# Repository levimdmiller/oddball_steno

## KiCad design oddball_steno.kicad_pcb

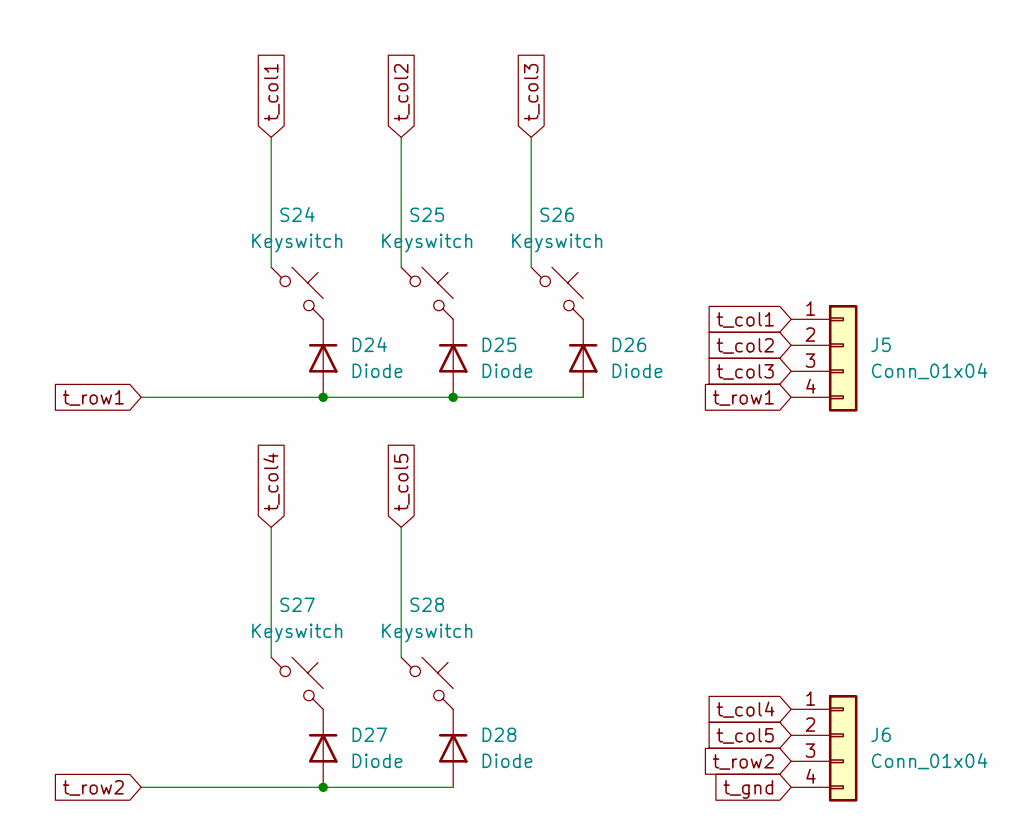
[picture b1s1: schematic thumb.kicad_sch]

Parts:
D24, D25, D26, D27, D28: Diode; Diode_DO-35
J5, J6: Conn_01x04; SolderWire-0.5sqmm_1x04_P4.6mm_D0.9mm_OD2.1mm
S24, S25, S26, S27, S28: Keyswitch; MX_PCB_1.00u

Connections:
unnamed: D24.1 (K), S24.2
unnamed: D25.1 (K), S25.2
unnamed: D26.1 (K), S26.2
unnamed: D27.1 (K), S27.2
unnamed: D28.1 (K), S28.2
t_col1: J5.1, S24.1
t_col2: J5.2, S25.1
t_col3: J5.3, S26.1
t_col4: J6.1, S27.1
t_col5: J6.2, S28.1
t_gnd: J6.4
t_row1: D24.2 (A), D25.2 (A), D26.2 (A), J5.4
t_row2: D27.2 (A), D28.2 (A), J6.3

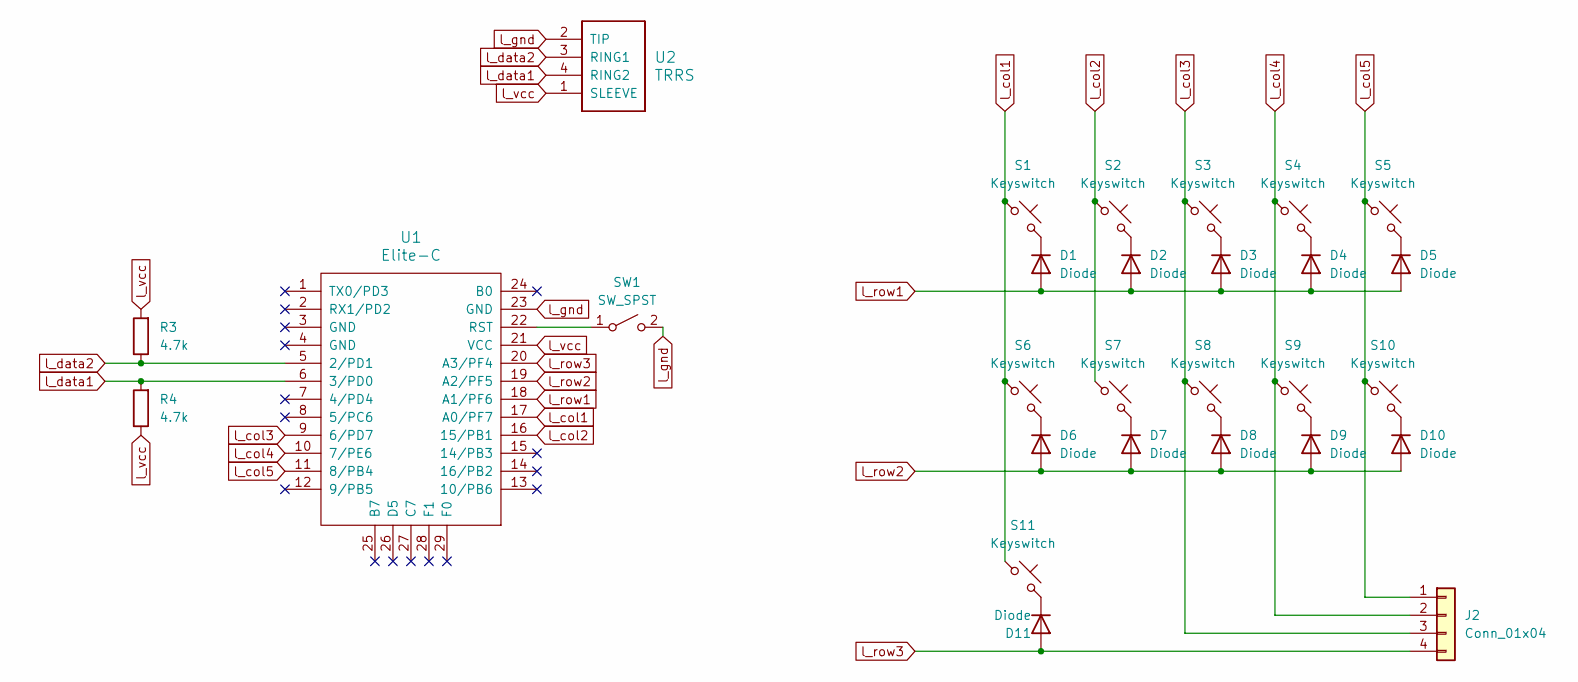
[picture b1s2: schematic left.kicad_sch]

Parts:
D1, D2, D3, D4, D5, D6, D7, D8, D9, D10, D11: Diode; Diode_DO-35
J2: Conn_01x04; SolderWire-0.5sqmm_1x04_P4.6mm_D0.9mm_OD2.1mm
R3, R4: 4.7k; Resistor
S1: Keyswitch; MX_PCB_4.00u
S2, S3, S4, S5, S7, S8, S9, S10: Keyswitch; MX_PCB_1.00u
S6, S11: Keyswitch; MX_PCB_2.00u_90deg
SW1: SW_SPST; SW_Push_1P1T_NO_CK_KSC6xxJ
U1: Elite-C
U2: TRRS; TRRS_PJ-320A

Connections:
unnamed: D1.1 (K), S1.2
unnamed: D2.1 (K), S2.2
unnamed: D3.1 (K), S3.2
unnamed: D4.1 (K), S4.2
unnamed: D5.1 (K), S5.2
unnamed: D6.1 (K), S6.2
unnamed: D7.1 (K), S7.2
unnamed: D8.1 (K), S8.2
unnamed: D9.1 (K), S9.2
unnamed: D10.1 (K), S10.2
unnamed: D11.1 (K), S11.2
unnamed: SW1.1 (A), U1.22 (RST)
l_col1: S1.1, S6.1, S11.1, U1.17 (A0/PF7)
l_col2: S2.1, S7.1, U1.16 (15/PB1)
l_col3: J2.3, S3.1, S8.1, U1.9 (6/PD7)
l_col4: J2.2, S4.1, S9.1, U1.10 (7/PE6)
l_col5: J2.1, S5.1, S10.1, U1.11 (8/PB4)
l_data1: R4.2, U1.6 (3/PD0), U2.4 (RING2)
l_data2: R3.1, U1.5 (2/PD1), U2.3 (RING1)
l_gnd: SW1.2 (B), U1.23 (GND), U2.2 (TIP)
l_row1: D1.2 (A), D2.2 (A), D3.2 (A), D4.2 (A), D5.2 (A), U1.18 (A1/PF6)
l_row2: D6.2 (A), D7.2 (A), D8.2 (A), D9.2 (A), D10.2 (A), U1.19 (A2/PF5)
l_row3: D11.2 (A), J2.4, U1.20 (A3/PF4)
l_vcc: R3.2, R4.1, U1.21 (VCC), U2.1 (SLEEVE)

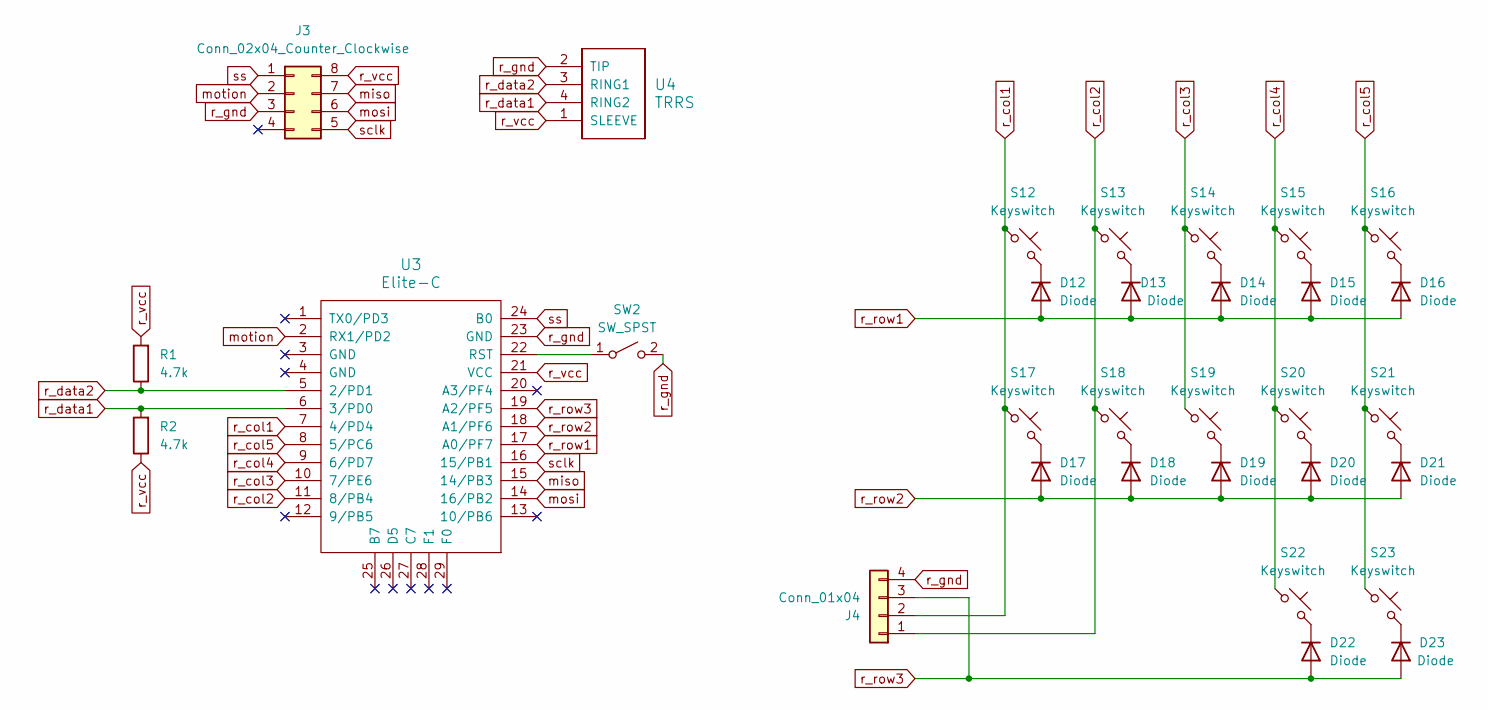
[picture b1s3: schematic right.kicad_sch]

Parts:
D12, D13, D14, D15, D16, D17, D18, D19, D20, D21, D22, D23: Diode; Diode_DO-35
J3: Conn_02x04_Counter_Clockwise; PinHeader_2x04_P2.54mm_Vertical
J4: Conn_01x04; SolderWire-0.5sqmm_1x04_P4.6mm_D0.9mm_OD2.1mm
R1, R2: 4.7k; Resistor
S12, S13, S14, S15, S16, S17, S18, S19, S20, S21: Keyswitch; MX_PCB_1.00u
S22: Keyswitch; MX_PCB_2.00u_90deg
S23: Keyswitch; MX_PCB_6.00u
SW2: SW_SPST; SW_Push_1P1T_NO_CK_KSC6xxJ
U3: Elite-C
U4: TRRS; TRRS_PJ-320A

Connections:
unnamed: D12.1 (K), S12.2
unnamed: D13.1 (K), S13.2
unnamed: D14.1 (K), S14.2
unnamed: D15.1 (K), S15.2
unnamed: D16.1 (K), S16.2
unnamed: D17.1 (K), S17.2
unnamed: D18.1 (K), S18.2
unnamed: D19.1 (K), S19.2
unnamed: D20.1 (K), S20.2
unnamed: D21.1 (K), S21.2
unnamed: D22.1 (K), S22.2
unnamed: D23.1 (K), S23.2
unnamed: SW2.1 (A), U3.22 (RST)
miso: J3.7, U3.15 (14/PB3)
mosi: J3.6, U3.14 (16/PB2)
motion: J3.2, U3.2 (RX1/PD2)
r_col1: J4.2, S12.1, S17.1, U3.7 (4/PD4)
r_col2: J4.1, S13.1, S18.1, U3.11 (8/PB4)
r_col3: S14.1, S19.1, U3.10 (7/PE6)
r_col4: S15.1, S20.1, S22.1, U3.9 (6/PD7)
r_col5: S16.1, S21.1, S23.1, U3.8 (5/PC6)
r_data1: R2.2, U3.6 (3/PD0), U4.4 (RING2)
r_data2: R1.1, U3.5 (2/PD1), U4.3 (RING1)
r_gnd: J3.3, J4.4, SW2.2 (B), U3.23 (GND), U4.2 (TIP)
r_row1: D12.2 (A), D13.2 (A), D14.2 (A), D15.2 (A), D16.2 (A), U3.17 (A0/PF7)
r_row2: D17.2 (A), D18.2 (A), D19.2 (A), D20.2 (A), D21.2 (A), U3.18 (A1/PF6)
r_row3: D22.2 (A), D23.2 (A), J4.3, U3.19 (A2/PF5)
r_vcc: J3.8, R1.2, R2.1, U3.21 (VCC), U4.1 (SLEEVE)
sclk: J3.5, U3.16 (15/PB1)
ss: J3.1, U3.24 (B0)

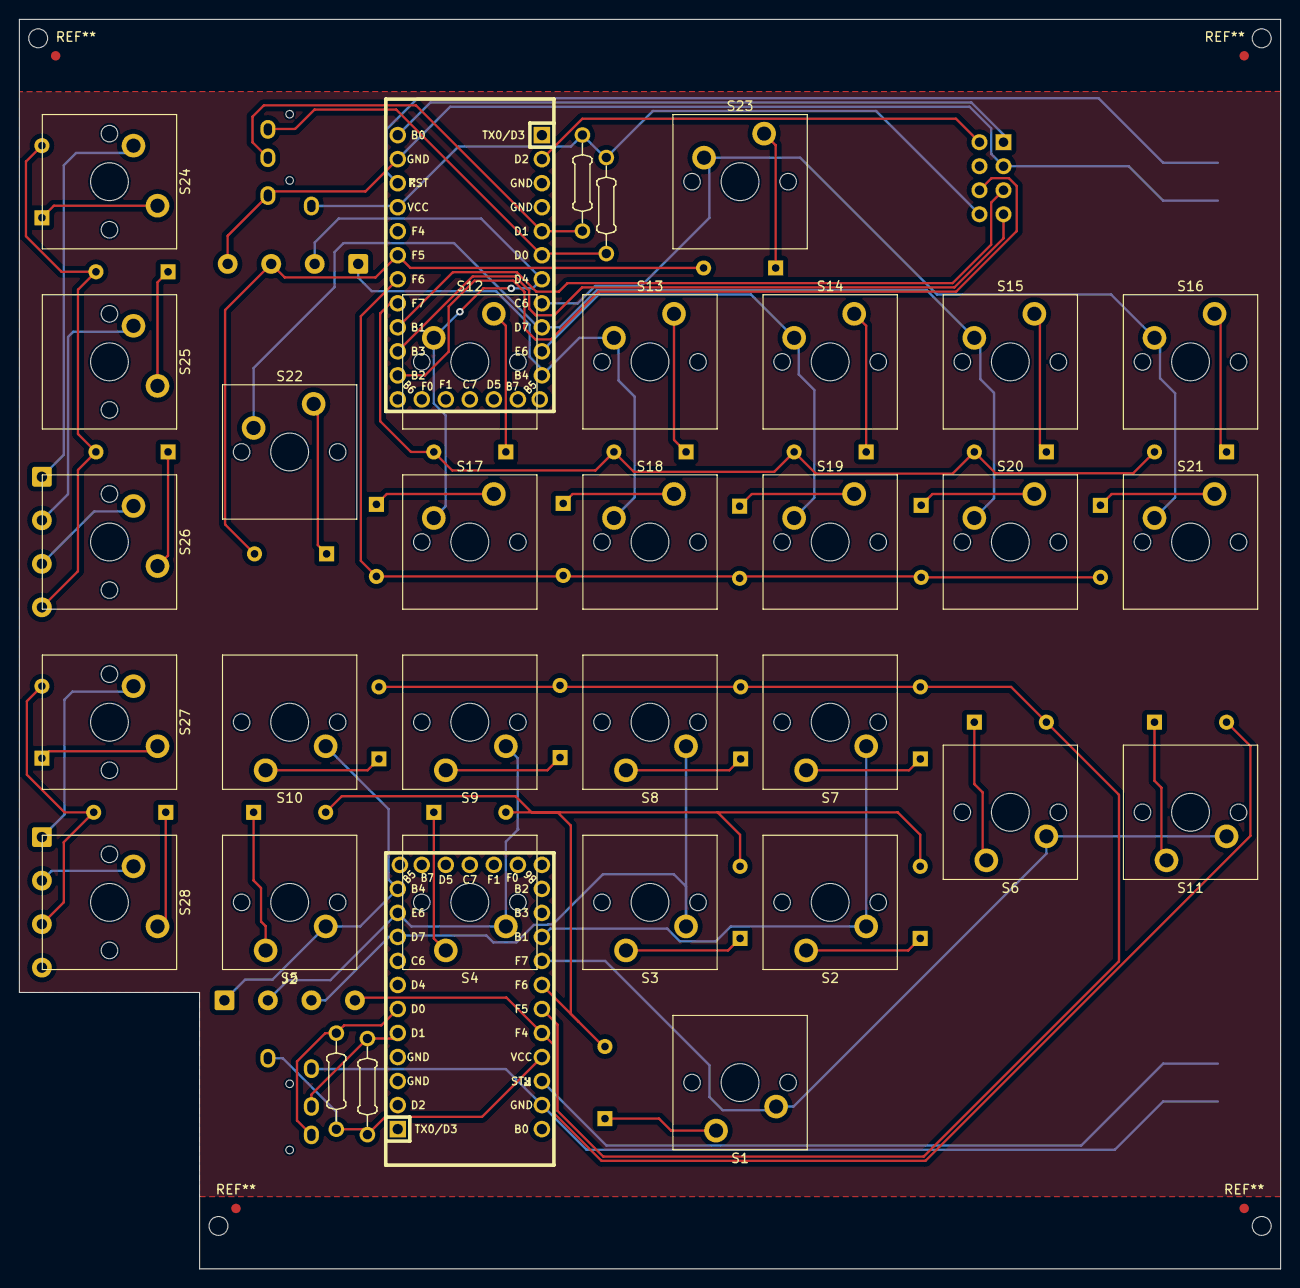
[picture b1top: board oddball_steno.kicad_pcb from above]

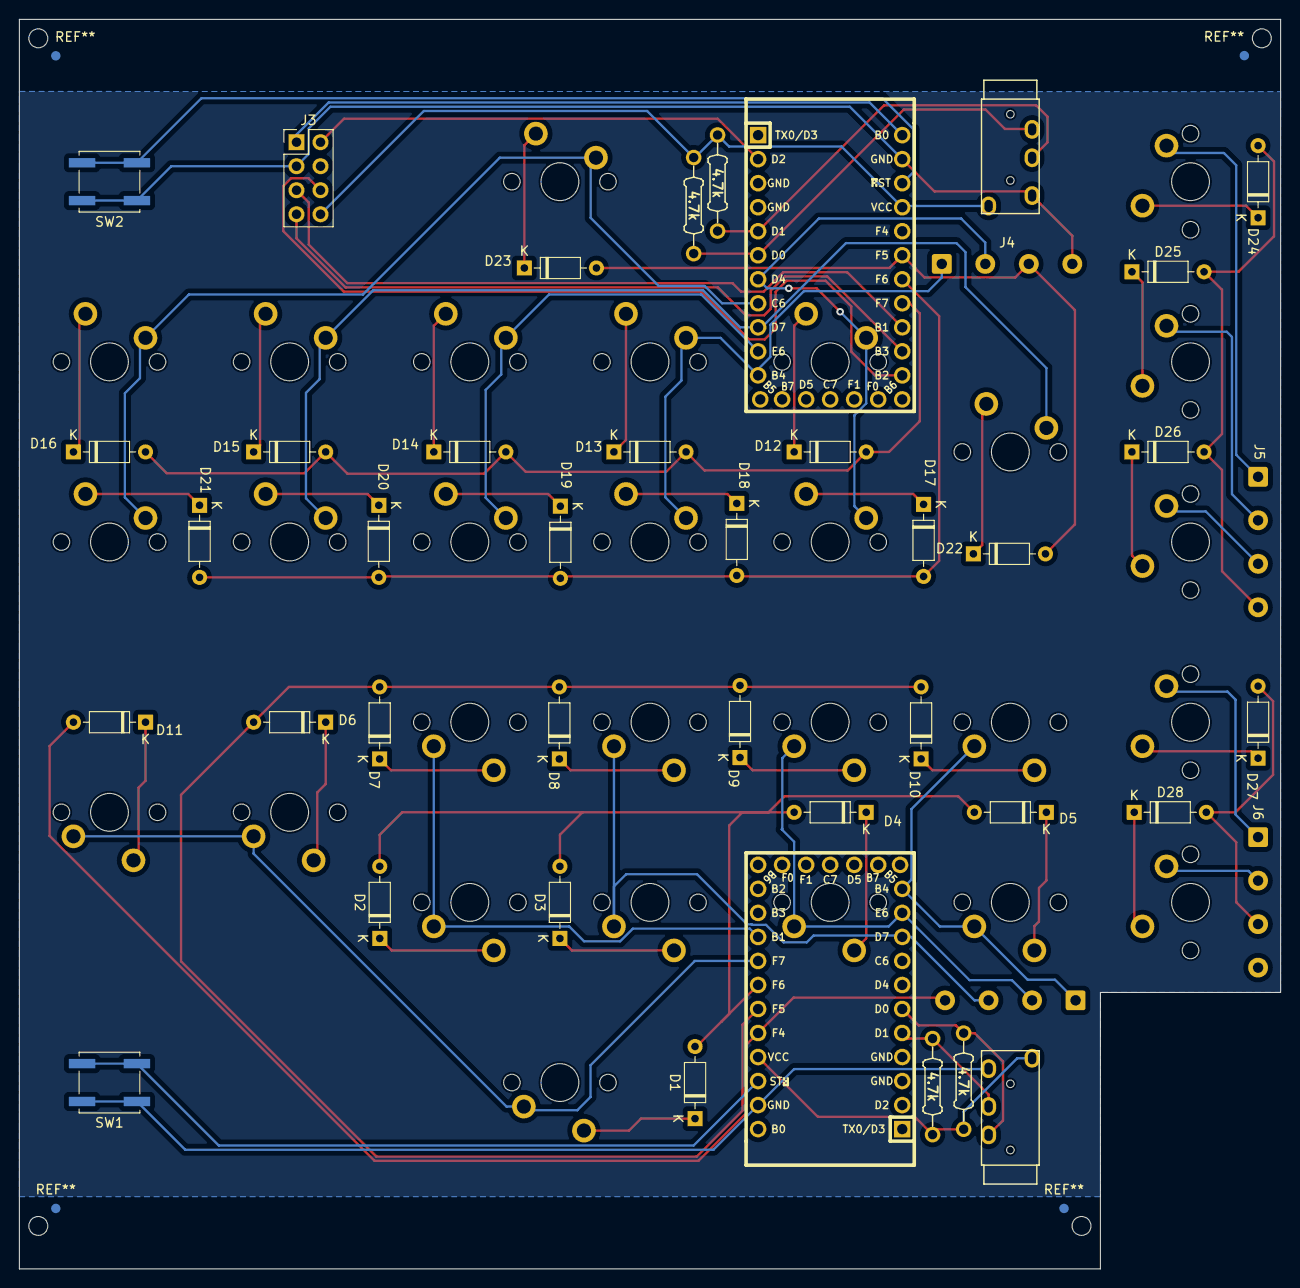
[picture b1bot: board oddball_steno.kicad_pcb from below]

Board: 2 copper layers, 133.3 x 132.1 mm, 71 parts (42 on the bottom side), 66 nets.

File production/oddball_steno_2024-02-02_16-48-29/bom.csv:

Designator,Footprint,Quantity,Value,LCSC Part #
"D1, D10, D11, D12, D13, D14, D15, D16, D17, D18, D19, D2, D20, D21, D22, D23, D24, D25, D26, D27, D28, D3, D4, D5, D6, D7, D8, D9",Diode_DO-35,28,Diode,
"J2, J4, J5, J6",SolderWire-0.5sqmm_1x04_P4.6mm_D0.9mm_OD2.1mm,4,Conn_01x04,
J3,PinHeader_2x04_P2.54mm_Vertical,1,Conn_02x04_Counter_Clockwise,
"R1, R2, R3, R4",Resistor,4,4.7k,
S1,MX_PCB_4.00u,1,Keyswitch,
"S10, S12, S13, S14, S15, S16, S17, S18, S19, S2, S20, S21, S24, S25, S26, S27, S28, S3, S4, S5, S7, S8, S9",MX_PCB_1.00u,23,Keyswitch,
"S11, S22, S6",MX_PCB_2.00u_90deg,3,Keyswitch,
S23,MX_PCB_6.00u,1,Keyswitch,
"SW1, SW2",SW_Push_1P1T_NO_CK_KSC6xxJ,2,SW_SPST,
"U1, U3",Elite-C,2,Elite-C,
"U2, U4",TRRS_PJ-320A,2,TRRS,

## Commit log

2024-02-01 Add pcb files
2024-02-01 Update edgecuts and add vscore
2024-02-03 Rearrange panelled board
2024-02-04 Add tooling holes and fiducials
2024-02-04 Add f.fab to build
2024-02-04 Add production build
2024-02-05 Make v-cut lines .15mm
2024-02-21 Add build
2024-02-25 Move kicad to subfolder
2024-02-25 Add keyboard layouts
2024-02-25 Copy models and update to ortho layout
2024-03-02 Update right case to match pcb
